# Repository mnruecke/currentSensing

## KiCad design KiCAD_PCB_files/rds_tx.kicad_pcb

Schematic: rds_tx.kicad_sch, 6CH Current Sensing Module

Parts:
C1, C4: 18p; C_0603_1608Metric_Pad1.08x0.95mm_HandSolder
C2, C3, C5, C6, C10, C11, C12, C20, C25: 100n; C_1206_3216Metric
C8: 100u; CP_Elec_10x12.5
H1, H2, H3, H4: Mounting; MountingHole_3.2mm_M3_DIN965_Pad
J1: LiPo_Akku; PinHeader_1x02_P2.54mm_Vertical
J2: board space lhs; PinHeader_1x26_P2.54mm_Vertical
J3: PSoC lhs; PinHeader_1x26_P2.54mm_Vertical
J4: PSoC rhs; PinHeader_1x26_P2.54mm_Vertical
J5: board space rhs; PinHeader_1x26_P2.54mm_Vertical
J6: BLE; PinHeader_1x04_P2.54mm_Vertical
J7: IP_A1; screw_conn_2
J8: IN_A1; screw_conn_2
J9: IP_B1; screw_conn_2
J10: IN_B1; screw_conn_2
J11: LiPo_Akku; screw_conn_2
J12: IP_C1; screw_conn_2
J13: IN_C1; screw_conn_2
J14: IP_Adjust_C1; PinSocket_1x05_P2.54mm_Vertical
J15: IN_Adjust_C1; PinSocket_1x05_P2.54mm_Vertical
J16: CurrentSensing; PinHeader_2x05_P2.54mm_Vertical
J17: IP_A2; screw_conn_2
J18: IN_A2; screw_conn_2
J19: IP_B2; screw_conn_2
J20: IN_B2; screw_conn_2
J21: IP_C2; screw_conn_2
J22: IN_C2; screw_conn_2
J23: IP_Adjust_C2; PinSocket_1x05_P2.54mm_Vertical
J24: IN_Adjust_C2; PinSocket_1x05_P2.54mm_Vertical
J25: GPIO_Block; PinHeader_2x05_P2.54mm_Vertical
J26: PWR_230V; screw_conn_2
J27: 6CH_Sense; PinHeader_2x12_P2.54mm_Vertical
J28: ACombi; BNC_TEConnectivity_1478204_Vertical
J29: ACombi; screw_conn_2
J70: IP_Adjust_A1; PinSocket_1x05_P2.54mm_Vertical
J71: IN_Adjust_A1; PinSocket_1x05_P2.54mm_Vertical
J72: IP_Adjust_B1; PinSocket_1x05_P2.54mm_Vertical
J73: IN_Adjust_B1; PinSocket_1x05_P2.54mm_Vertical
J74: IP_Adjust_A2; PinSocket_1x05_P2.54mm_Vertical
J75: IN_Adjust_A2; PinSocket_1x05_P2.54mm_Vertical
J76: IP_Adjust_B2; PinSocket_1x05_P2.54mm_Vertical
J77: IN_Adjust_B2; PinSocket_1x05_P2.54mm_Vertical
R1, R2: 0; R_0603_1608Metric_Pad0.98x0.95mm_HandSolder
U1: XC6227; LDO_3p3V_XC6227
U2, U3, U33, U34, U35, U36: MCA1101; SOIC-16W_7.5x12.8mm_P1.27mm
U37: ECE5
U38: L7805; TO-220-3_Vertical
U39: RAC03; ACDC_RAC03
Y1: 18 MHz; ABLS_Crystal_18MHz_SMD

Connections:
+5V: C2.1, C3.1, C6.1, C8.1, J1.1, J2.26, J3.26, J4.1, J5.1, J6.1, J11.1, J16.9, J25.9, U1.1 (CE), U1.4 (VIN), U38.3 (OUT)
/ACL: J26.1, U37.2 (ACL), U39.1 (ACL)
/ACN: J26.2, U37.1 (ACN), U39.4 (ACN)
/Aout+: J4.5, J5.5, J28.1 (In), J29.2
/Aout-: J4.6, J5.6, R1.1
/ISenseN_A1: J2.3, J3.3, J27.22, U33.13 (Vref)
/ISenseN_A2: J2.6, J3.6, J27.10, U35.13 (Vref)
/ISenseN_B1: J2.8, J3.8, J27.18, U34.13 (Vref)
/ISenseN_B2: J2.17, J3.17, J27.6, U36.13 (Vref)
/ISenseN_C1: J2.22, J3.22, J27.14, U2.13 (Vref)
/ISenseN_C2: J4.23, J5.23, J27.2, U3.13 (Vref)
/ISenseP_A1: J2.2, J3.2, J16.3, J27.24, U33.12 (Vout)
/ISenseP_A2: J2.5, J3.5, J16.4, J27.12, U35.12 (Vout)
/ISenseP_B1: J2.7, J3.7, J16.5, J27.20, U34.12 (Vout)
/ISenseP_B2: J2.16, J3.16, J16.6, J27.8, U36.12 (Vout)
/ISenseP_C1: J2.21, J3.21, J16.7, J27.16, U2.12 (Vout)
/ISenseP_C2: J4.22, J5.22, J16.8, J27.4, U3.12 (Vout)
/P12.0: J4.11, J5.11, J25.1
/P12.1: J4.12, J5.12, J25.2
/P12.2: J4.13, J5.13, J25.3
/P12.3: J4.14, J5.14, J25.4
/P12.4: J4.15, J5.15, J25.5
/P12.5: J4.16, J5.16, J25.6
/P12.6: J4.17, J5.17, J25.7
/P12.7: J4.18, J5.18, J25.8
/XTALn: C1.2, J2.10, J3.10, Y1.2
/XTALp: C4.1, J2.11, J3.11, Y1.1
/senseA1+: J7.1, J7.2, J70.1, J70.2, J70.3, J70.4, J70.5, U33.5 (IP-), U33.6 (IP-), U33.7 (IP-), U33.8 (IP-)
/senseA1-: J8.1, J8.2, J71.1, J71.2, J71.3, J71.4, J71.5, U33.1 (IP+), U33.2 (IP+), U33.3 (IP+), U33.4 (IP+)
/senseA2+: J17.1, J17.2, J74.1, J74.2, J74.3, J74.4, J74.5, U35.5 (IP-), U35.6 (IP-), U35.7 (IP-), U35.8 (IP-)
/senseA2-: J18.1, J18.2, J75.1, J75.2, J75.3, J75.4, J75.5, U35.1 (IP+), U35.2 (IP+), U35.3 (IP+), U35.4 (IP+)
/senseB1+: J9.1, J9.2, J72.1, J72.2, J72.3, J72.4, J72.5, U34.5 (IP-), U34.6 (IP-), U34.7 (IP-), U34.8 (IP-)
/senseB1-: J10.1, J10.2, J73.1, J73.2, J73.3, J73.4, J73.5, U34.1 (IP+), U34.2 (IP+), U34.3 (IP+), U34.4 (IP+)
/senseB2+: J19.1, J19.2, J76.1, J76.2, J76.3, J76.4, J76.5, U36.5 (IP-), U36.6 (IP-), U36.7 (IP-), U36.8 (IP-)
/senseB2-: J20.1, J20.2, J77.1, J77.2, J77.3, J77.4, J77.5, U36.1 (IP+), U36.2 (IP+), U36.3 (IP+), U36.4 (IP+)
/senseC1+: J12.1, J12.2, J14.1, J14.2, J14.3, J14.4, J14.5, U2.5 (IP-), U2.6 (IP-), U2.7 (IP-), U2.8 (IP-)
/senseC1-: J13.1, J13.2, J15.1, J15.2, J15.3, J15.4, J15.5, U2.1 (IP+), U2.2 (IP+), U2.3 (IP+), U2.4 (IP+)
/senseC2+: J21.1, J21.2, J23.1, J23.2, J23.3, J23.4, J23.5, U3.5 (IP-), U3.6 (IP-), U3.7 (IP-), U3.8 (IP-)
/senseC2-: J22.1, J22.2, J24.1, J24.2, J24.3, J24.4, J24.5, U3.1 (IP+), U3.2 (IP+), U3.3 (IP+), U3.4 (IP+)
/sig1: J4.20, J5.20, J16.1
/sig2: J4.21, J5.21, J16.2
GND: C1.1, C2.2, C3.2, C4.2, C5.2, C6.2, C8.2, C10.2, C11.2, C12.2, C20.2, C25.2, H2.1, H3.1, H4.1, J1.2, J2.1, J2.25, J3.1, J3.25, J4.2, J5.2, J6.2, J11.2, J16.10, J25.10, J27.1, J27.3, J27.5, J27.7, J27.9, J27.11, J27.13, J27.15, J27.17, J27.19, J27.21, J27.23, R2.1, U1.2 (VSS), U2.11 (GND), U2.14 (GND), U2.15 (GND), U3.11 (GND), U3.14 (GND), U3.15 (GND), U33.11 (GND), U33.14 (GND), U33.15 (GND), U34.11 (GND), U34.14 (GND), U34.15 (GND), U35.11 (GND), U35.14 (GND), U35.15 (GND), U36.11 (GND), U36.14 (GND), U36.15 (GND), U37.4 (Vout-), U38.2 (GND), U39.2 (-Vout)
unnamed: J2.4, J3.4
unnamed: J2.9, J3.9
unnamed: J2.12, J3.12
unnamed: J2.13, J3.13
unnamed: J2.14, J3.14
unnamed: J2.15, J3.15
unnamed: J2.18, J3.18
unnamed: J2.19, J3.19
unnamed: J2.20, J3.20
unnamed: J2.23, J3.23
unnamed: J2.24, J3.24
unnamed: J4.3, J5.3, J6.3
unnamed: J4.4, J5.4, J6.4
unnamed: J4.7, J5.7
unnamed: J4.8, J5.8
unnamed: J4.9, J5.9
unnamed: J4.10, J5.10
unnamed: J4.19, J5.19
unnamed: J4.24, J5.24
unnamed: J4.25, J5.25
unnamed: J4.26, J5.26
unnamed: J28.2 (Ext), J29.1, R1.2, R2.2
unnamed: U37.5 (Vout+), U38.1 (IN), U39.3 (+Vout)

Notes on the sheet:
3.6
1.0
3.2
VDD
12.7
GND
PSoC, BLE
15.1
RST
0.4
1.4
2.0
3.7
Connectors
0.3
15.0
3.0
1.3
6x MCA1101
1.6
15.5
12.0
0.1
0.5
15.4
15.2
1.1
2.2
1.7
2.1
20,32 mm
0.7
0.6
LED
1.5
Power
15.3
0.2
1.2
3.4

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
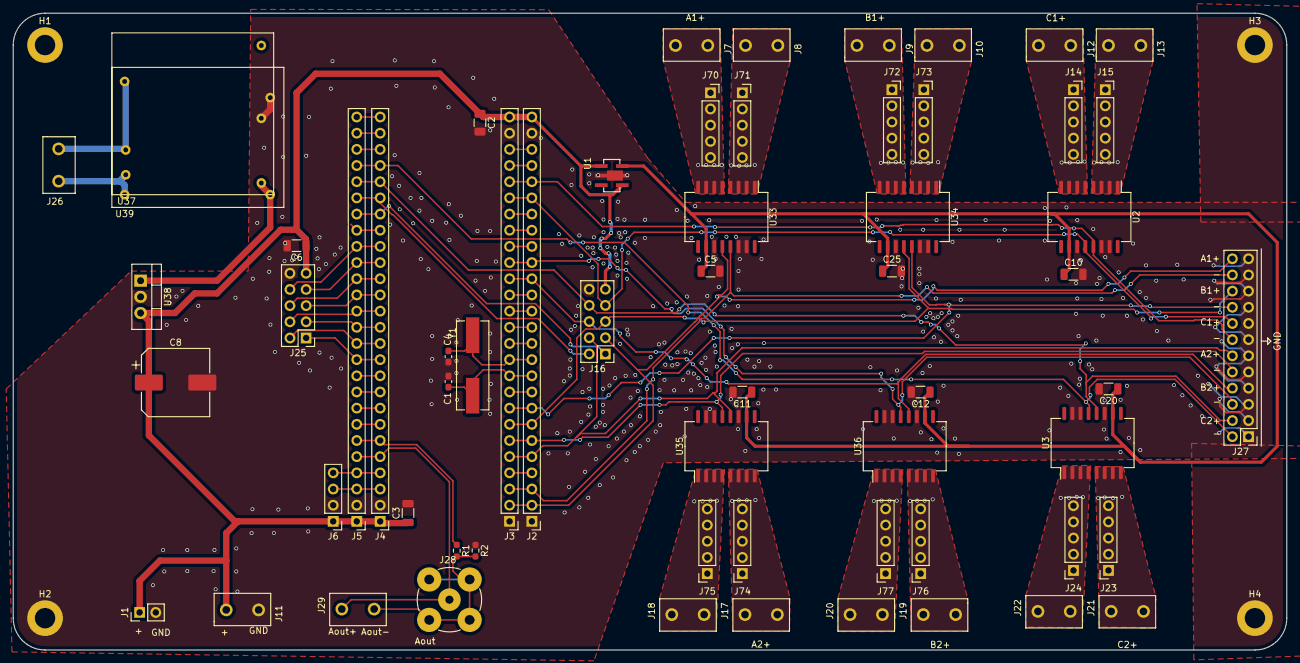
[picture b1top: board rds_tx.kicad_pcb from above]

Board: 2 copper layers, 200.0 x 100.0 mm, 66 parts (0 on the bottom side), 66 nets.

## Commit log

2023-02-02 currentSensing 20230202
2023-02-02 modified *.py script, switched from DMA to ISR version
2023-02-02 git test.. ..
2023-02-03 currentSens. ISR -> HC05 module + ext. 18 MHz Osz
2023-02-03 fix var collision with 'time' var
2023-02-03 add pdf with firmware schematic for the ISR version
2023-02-03 add uart command 'h' for sending only first 60 bytes
2023-02-04 add HC05 Bluetooth module programmer script
2023-02-04 switch back to 115200 Baud (ISR version)
2023-02-04 calibrate adc readout in *.py script
2023-02-05 add analog trigger input (ISR version) for triggering of current signals
2023-02-05 minor naming adjustments, swich 18 MHz XTAL back on
2023-02-07 add KiCAD PCB files to repo
2023-02-15 add example for 32 bit access of 4x 8 bit components (DACs)
2023-02-15 minor corrections in 32bit DAC access example
2023-03-07 start DMA version with 2Ms total
